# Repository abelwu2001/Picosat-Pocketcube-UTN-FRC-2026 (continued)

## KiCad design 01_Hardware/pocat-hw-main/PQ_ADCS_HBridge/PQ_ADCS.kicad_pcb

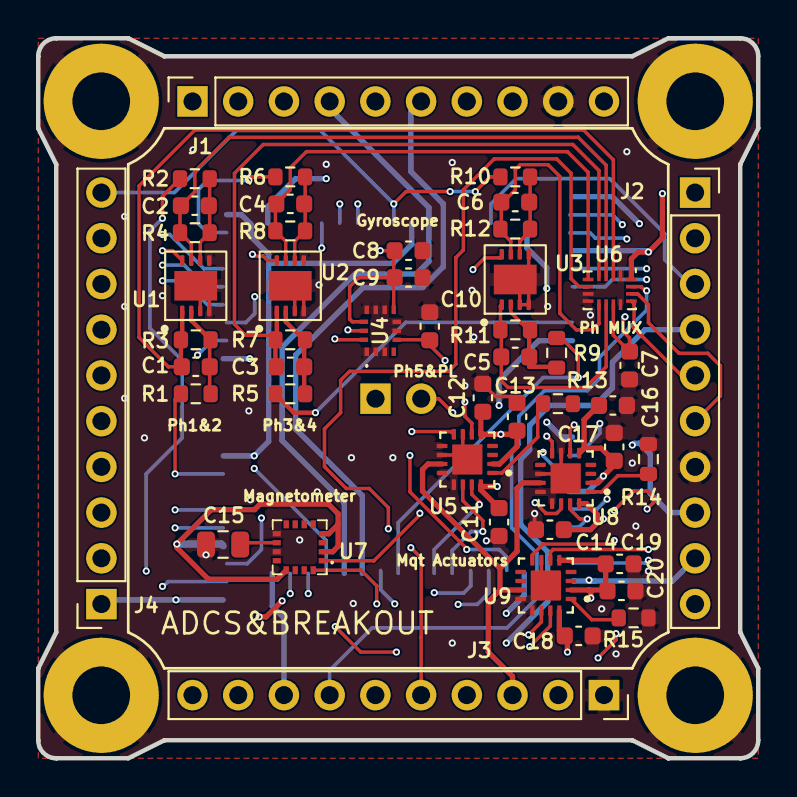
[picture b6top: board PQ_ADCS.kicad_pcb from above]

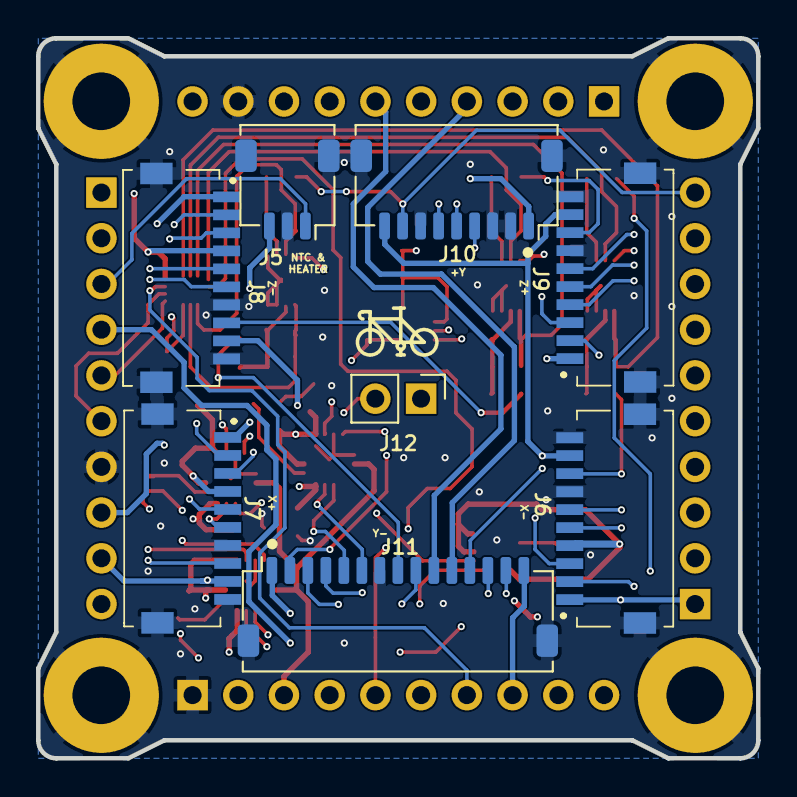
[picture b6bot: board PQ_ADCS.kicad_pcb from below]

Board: 6 copper layers, 40.0 x 40.0 mm, 61 parts (9 on the bottom side), 53 nets.

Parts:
Annotation1: Silkscreen_Annotation; Bike
C1, C2, C3, C4, C5, C6: 100 pF; C_0603_1608Metric
C7: 1 uF; C_0603_1608Metric
C8: 2.2 uF; C_0603_1608Metric
C9: 100 nF; C_0603_1608Metric
C10: 10 nF; C_0603_1608Metric
C11, C12, C14, C16, C18, C19: 100n; C_0603_1608Metric
C13, C17, C20: 10u; C_0603_1608Metric
C15: 10 uF; C_0805_2012Metric
H1, H2, H3, H4: MountingHole_Pad; MountingHole_3.2mm_M3_Pad
J1, J2, J3, J4: CES-110-02-L-S; SLW-110-01
J5: Pico-Clasp_01x03; Picoclasp03
J6, J7, J8, J9: Pico-Clasp_01x10; Picoclasp10
J10: Pico-Clasp_01x09; Picoclasp09
J11: Pico-Clasp_01x15; Picoclasp15
J12: CES-102-02-L-S; CES-102-02
R1, R2, R5, R6, R9, R10: 100; R_0603_1608Metric
R3, R4, R7, R8, R11, R12: 2k; R_0603_1608Metric
R13, R14, R15: 22k; R_0603_1608Metric
U1, U2, U3: LPV542; TI_X1SON-8_3x3mm
U4: IIM-42652; IIM42652
U5, U8, U9: DRV8214RTER; IC_DRV8214RTER
U6: TMUX1108RSVR; UQFN-16_1.8x2.6_Pitch0.4mm
U7: MMC5983MA

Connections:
3V3_PERM: C7.1, C8.1, C9.1, C10.1, C11.2, C12.1, C13.1, C14.2, C16.1, C17.1, C18.2, C19.1, C20.1, J1.10, J6.4, J7.4, J8.4, J9.4, J10.4, J11.4, U1.8 (V+), U2.8 (V+), U3.8 (V+), U4.5 (VDDIO), U4.8 (VDD), U4.12 (CS), U5.2 (VCC), U5.5 (VM), U5.16 (VREF), U6.11 (VDD), U6.16 (EN), U7.2 (VDD), U7.4 (SPI_CS), U7.13 (VDDIO), U8.2 (VCC), U8.5 (VM), U8.16 (VREF), U9.2 (VCC), U9.5 (VM), U9.16 (VREF)
/+MAG+X: J7.2, U5.6 (OUT1)
/+MAG+Y: J12.2, U8.6 (OUT1)
/+MAG+Z: J9.2, U9.6 (OUT1)
/+MAG-X: J6.2, J7.3
/+MAG-Y: J11.2, J12.1
/+MAG-Z: J8.2, J9.3
/-MAG-X: J6.3, U5.8 (OUT2)
/-MAG-Y: J11.3, U8.8 (OUT2)
/-MAG-Z: J8.3, U9.8 (OUT2)
/PHT1: J6.8, R1.1
/PHT1_ADCS: C1.1, R3.2, U1.1 (OUT_A), U6.2 (S1)
/PHT2: J7.8, R2.1
/PHT2_ADCS: C2.2, R4.1, U1.7 (OUT_B), U6.3 (S2)
/PHT3: J8.8, R5.1
/PHT3_ADCS: C3.1, R7.2, U2.1 (OUT_A), U6.4 (S3)
/PHT4: J9.8, R6.1
/PHT4_ADCS: C4.2, R8.1, U2.7 (OUT_B), U6.5 (S4)
/PHT5: J11.8, R9.1
/PHT5_ADCS: C5.1, R11.2, U3.1 (OUT_A), U6.10 (S5)
/PHT6_ADCS: C6.2, R12.1, U3.7 (OUT_B), U6.9 (S6)
ADCS_POWER: J3.3, U5.11 (~SLEEP), U8.11 (~SLEEP), U9.11 (~SLEEP)
ADC_PH: J3.5, U6.6 (D)
BATT-: J1.6, J11.10
BATT_NTC: J2.3, J5.1
BURNCOMMS: J2.9, J6.9, J7.9, J8.9, J9.9, J10.9
GND: C7.2, C8.2, C9.2, C10.2, C11.1, C12.2, C13.2, C14.1, C15.2, C16.2, C17.2, C18.1, C19.2, C20.2, H1.1, H2.1, H3.1, H4.1, J1.9, J2.7, J3.1, J5.2, J5.MP, J6.7, J6.10, J6.MP, J7.7, J7.10, J7.MP, J8.7, J8.10, J8.MP, J9.7, J9.10, J9.MP, J10.2, J10.3, J10.7, J10.MP, J11.7, J11.MP, R13.2, R14.2, R15.2, U1.3 (+IN_A), U1.4 (V-), U1.5 (+IN_B), U1.9 (EPAD), U2.3 (+IN_A), U2.4 (V-), U2.5 (+IN_B), U2.9 (EPAD), U3.3 (+IN_A), U3.4 (V-), U3.5 (+IN_B), U3.9 (EPAD), U4.1 (SDO/AD0), U4.2 (RESV1), U4.3 (RESV2), U4.6 (GND), U4.7 (RESV3), U4.9 (INT2/FSYNC/CLKIN), U4.10 (RESV4), U4.11 (RESV5), U5.7 (GND), U5.9 (A1), U5.10 (A0), U5.12 (PH/IN2), U5.13 (EN/IN1), U5.17 (EXP), U6.1 (VSS), U6.7 (S8), U6.8 (S7), U6.12 (GND), U7.9 (GND_1), U7.11 (GND_2), U8.7 (GND), U8.10 (A0), U8.12 (PH/IN2), U8.13 (EN/IN1), U8.17 (EXP), U9.7 (GND), U9.12 (PH/IN2), U9.13 (EN/IN1), U9.17 (EXP)
HEATER_PWR: J2.8, J5.3
KILLSWITCH+: J1.4, J11.11
NRST: J4.5, J11.12
unnamed: C1.2, R1.2, R3.1, U1.2 (-IN_A)
unnamed: C2.1, R2.2, R4.2, U1.6 (-IN_B)
unnamed: C3.2, R5.2, R7.1, U2.2 (-IN_A)
unnamed: C4.1, R6.2, R8.2, U2.6 (-IN_B)
unnamed: C5.2, R9.2, R11.1, U3.2 (-IN_A)
unnamed: C6.1, R10.2, R12.2, U3.6 (-IN_B)
unnamed: R13.1, U5.1 (IPROPI)
unnamed: C15.1, U7.10 (CAP)
unnamed: R14.1, U8.1 (IPROPI)
unnamed: R15.1, U9.1 (IPROPI)
PH_PL: J4.10, J10.8, R10.1
SCL3: J1.7, J6.6, J7.6, J8.6, J9.6, J10.6, J11.6, U4.13 (SCL/SCLK), U5.15 (SCL), U7.1 (SCL/SPI_SCK), U8.15 (SCL), U9.15 (SCL)
SDA3: J4.4, J6.5, J7.5, J8.5, J9.5, J10.5, J11.5, U4.14 (SDA/SDIO/SDI), U5.14 (SDA), U7.16 (SDA/SPI_SDI), U8.14 (SDA), U9.14 (SDA)
SEL_PH0: J3.7, U6.15 (A0)
SEL_PH1: J2.6, U6.14 (A1)
SEL_PH2: J2.5, U6.13 (A2)
SOLAR_X: J4.1, J6.1, J7.1
SOLAR_Y: J2.4, J10.1, J11.1
SOLAR_Z: J2.10, J8.1, J9.1
SWCLK: J4.7, J11.13
SWDIO: J4.6, J11.14
SWO: J2.2, J11.9
VCC_UMBILICAL: J3.8, J11.15
